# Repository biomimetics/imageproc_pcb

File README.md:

imageproc-pcb
=============

ImageProc printed circuit board

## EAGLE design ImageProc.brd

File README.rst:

This work is licensed under the `Creative Commons Attribution 3.0
Unported License <http://creativecommons.org/licenses/by/3.0/>`_.

================================
ImageProc printed circuit boards
================================

Description:
 ImageProc family of printed circuit boards, which use Microchip's dsPIC
 architecture.

Download boards:
 https://github.com/biomimetics/imageproc_pcb

Citing the boards:
 If you would like to reference these boards in a publication, please
 refer to the url and cite these conference papers:

 - *For ImageProc v.1.x:*

   | Fernando L. Garcia Bermudez and Ronald S. Fearing (2009)
   | `Optical Flow on a Flapping Wing Robot
     <http://dx.doi.org/10.1109/IROS.2009.5354337>`_
   | In IROS 2009. St. Louis, MO, USA.

 - *For ImageProc v.2.0-v2.4-x:*

   | Stanley S. Baek, Fernando L. Garcia Bermudez, and Ronald S. Fearing (2011)
   | `Flight Control for Target Seeking by 13 gram Ornithopter
     <http://dx.doi.org/10.1109/IROS.2011.6094581>`_
   | In IROS 2011. San Francisco, CA, USA.

 - *For ImageProc v2.5-x:*

   | Ryan C. Julian, Douglas D. Hutchings, and Ronald S. Fearing (2012)
   | This design is pending publication.

 This material is based upon work supported by the National Science
 Foundation under Grant No. IIS-0705429 and IIS-0931463. Any opinions,
 findings, and conclusions or recommendations expressed in this material
 are those of the author(s) and do not necessarily reflect the views of
 the National Science Foundation.

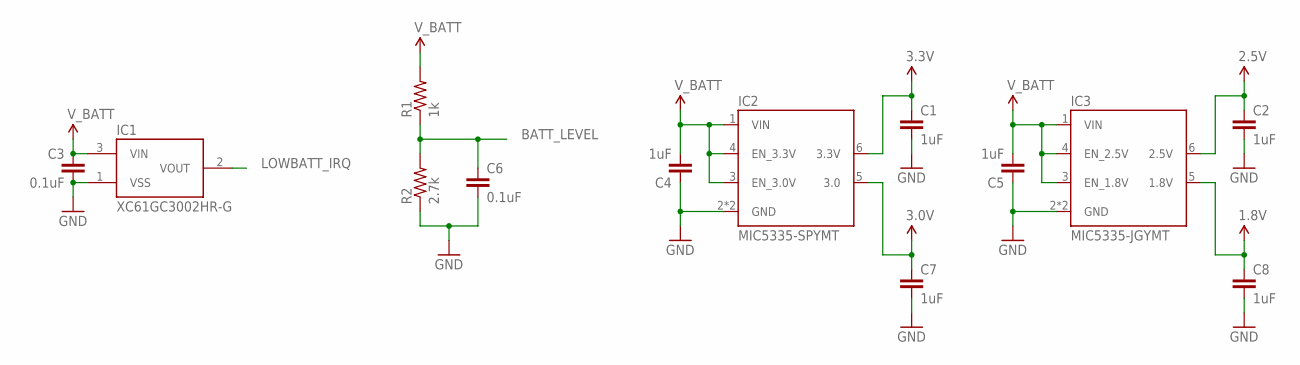
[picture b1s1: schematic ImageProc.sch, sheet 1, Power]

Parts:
C1, C2, C4, C5, C7, C8: 1uF; 0402-CAP
C3, C6: 0.1uF; 0402-CAP
IC1: XC61GC3002HR-G; USP-3
IC2: MIC5335-SPYMT; MLF-6
IC3: MIC5335-JGYMT; MLF-6
R1: 1k; 0402-RES
R2: 2.7k; 0402-RES

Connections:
1.8V: C8.1, IC3.5 (1.8V); also elsewhere on the board
2.5V: C2.1, IC3.6 (2.5V); also elsewhere on the board
3.0V: C7.1, IC2.5 (3.0)
3.3V: C1.1, IC2.6 (3.3V); also elsewhere on the board
BATT_LEVEL: C6.1, R1.1, R2.2; also elsewhere on the board
GND: C1.2, C2.2, C3.2, C4.1, C5.1, C6.2, C7.2, C8.2, IC1.1 (VSS), IC2.2 (GND), IC2.EPAD (GND), IC3.2 (GND), IC3.EPAD (GND), R2.1; also elsewhere on the board
LOWBATT_IRQ: IC1.2 (VOUT); also elsewhere on the board
V_BATT: C3.1, C4.2, C5.2, IC1.3 (VIN), IC2.1 (VIN), IC2.3 (EN_3.0V), IC2.4 (EN_3.3V), IC3.1 (VIN), IC3.3 (EN_1.8V), IC3.4 (EN_2.5V), R1.2; also elsewhere on the board

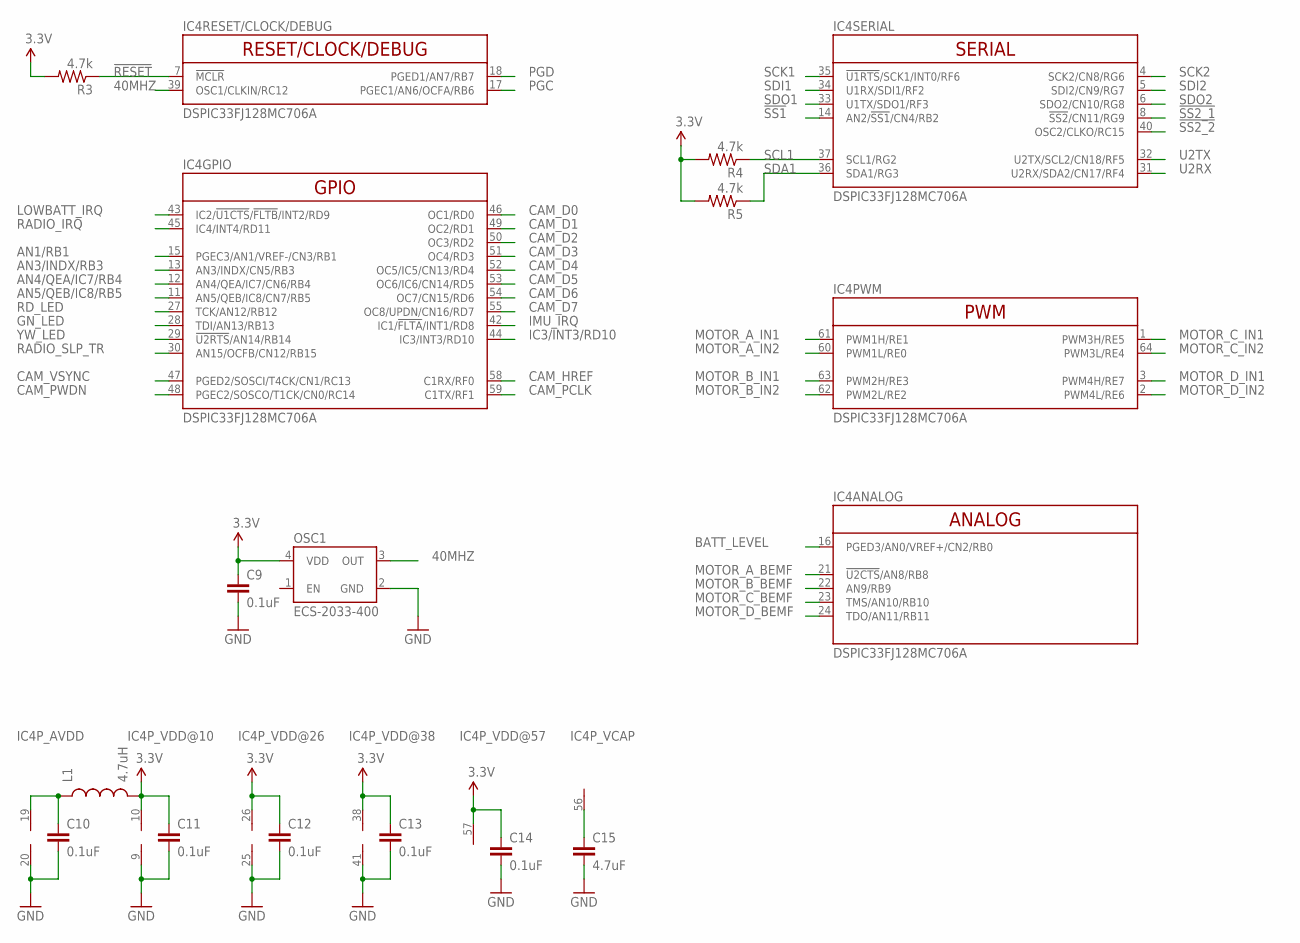
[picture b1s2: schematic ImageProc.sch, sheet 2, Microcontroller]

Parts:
C9, C10, C11, C12, C13, C14: 0.1uF; 0402-CAP
C15: 4.7uF; 0603-CAP; VOLTAGE 16V
IC4: DSPIC33FJ128MC706A; TQFP-64
L1: 4.7uH; 0603
OSC1: ECS-2033-400; OSCILLATOR-SMD
R3, R4, R5: 4.7k; 0402-RES

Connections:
3.3V: C9.1, C11.1, C12.1, C13.1, C14.1, IC4.10 (V+), IC4.26 (V+), IC4.38 (V+), IC4.57 (V+), L1.2, OSC1.4 (VDD), R3.2, R4.2, R5.2; also elsewhere on the board
40MHZ: IC4.39 (OSC1/CLKIN/RC12), OSC1.3 (OUT); also elsewhere on the board
!RESET: IC4.7 (!MCLR), R3.1; also elsewhere on the board
!SS1: IC4.14 (AN2/!SS1!/CN4/RB2); also elsewhere on the board
!SS2_1: IC4.8 (!SS2!/CN11/RG9); also elsewhere on the board
!SS2_2: IC4.40 (OSC2/CLKO/RC15); also elsewhere on the board
AN1/RB1: IC4.15 (PGEC3/AN1/VREF-/CN3/RB1); also elsewhere on the board
AN3/INDX/RB3: IC4.13 (AN3/INDX/CN5/RB3); also elsewhere on the board
AN4/QEA/IC7/RB4: IC4.12 (AN4/QEA/IC7/CN6/RB4); also elsewhere on the board
AN5/QEB/IC8/RB5: IC4.11 (AN5/QEB/IC8/CN7/RB5); also elsewhere on the board
BATT_LEVEL: IC4.16 (PGED3/AN0/VREF+/CN2/RB0); also elsewhere on the board
CAM_D0: IC4.46 (OC1/RD0); also elsewhere on the board
CAM_D1: IC4.49 (OC2/RD1); also elsewhere on the board
CAM_D2: IC4.50 (OC3/RD2); also elsewhere on the board
CAM_D3: IC4.51 (OC4/RD3); also elsewhere on the board
CAM_D4: IC4.52 (OC5/IC5/CN13/RD4); also elsewhere on the board
CAM_D5: IC4.53 (OC6/IC6/CN14/RD5); also elsewhere on the board
CAM_D6: IC4.54 (OC7/CN15/RD6); also elsewhere on the board
CAM_D7: IC4.55 (OC8/UPDN/CN16/RD7); also elsewhere on the board
CAM_HREF: IC4.58 (C1RX/RF0); also elsewhere on the board
CAM_PCLK: IC4.59 (C1TX/RF1); also elsewhere on the board
CAM_PWDN: IC4.48 (PGEC2/SOSCO/T1CK/CN0/RC14); also elsewhere on the board
CAM_VSYNC: IC4.47 (PGED2/SOSCI/T4CK/CN1/RC13); also elsewhere on the board
GND: C9.2, C10.2, C11.2, C12.2, C13.2, C14.2, C15.2, IC4.9 (V-), IC4.20 (V-), IC4.25 (V-), IC4.41 (V-), OSC1.2 (GND); also elsewhere on the board
GN_LED: IC4.28 (TDI/AN13/RB13); also elsewhere on the board
IC3/INT3/RD10: IC4.44 (IC3/INT3/RD10); also elsewhere on the board
IMU_IRQ: IC4.42 (IC1/!FLTA!/INT1/RD8); also elsewhere on the board
LOWBATT_IRQ: IC4.43 (IC2/!U1CTS!/!FLTB!/INT2/RD9); also elsewhere on the board
MOTOR_A_BEMF: IC4.21 (!U2CTS!/AN8/RB8); also elsewhere on the board
MOTOR_A_IN1: IC4.61 (PWM1H/RE1); also elsewhere on the board
MOTOR_A_IN2: IC4.60 (PWM1L/RE0); also elsewhere on the board
MOTOR_B_BEMF: IC4.22 (AN9/RB9); also elsewhere on the board
MOTOR_B_IN1: IC4.63 (PWM2H/RE3); also elsewhere on the board
MOTOR_B_IN2: IC4.62 (PWM2L/RE2); also elsewhere on the board
MOTOR_C_BEMF: IC4.23 (TMS/AN10/RB10); also elsewhere on the board
MOTOR_C_IN1: IC4.1 (PWM3H/RE5); also elsewhere on the board
MOTOR_C_IN2: IC4.64 (PWM3L/RE4); also elsewhere on the board
MOTOR_D_BEMF: IC4.24 (TDO/AN11/RB11); also elsewhere on the board
MOTOR_D_IN1: IC4.3 (PWM4H/RE7); also elsewhere on the board
MOTOR_D_IN2: IC4.2 (PWM4L/RE6); also elsewhere on the board
unnamed: C10.1, IC4.19 (V+), L1.1
unnamed: C15.1, IC4.56 (V+)
PGC: IC4.17 (PGEC1/AN6/OCFA/RB6); also elsewhere on the board
PGD: IC4.18 (PGED1/AN7/RB7); also elsewhere on the board
RADIO_IRQ: IC4.45 (IC4/INT4/RD11); also elsewhere on the board
RADIO_SLP_TR: IC4.30 (AN15/OCFB/CN12/RB15); also elsewhere on the board
RD_LED: IC4.27 (TCK/AN12/RB12); also elsewhere on the board
SCK1: IC4.35 (!U1RTS!/SCK1/INT0/RF6); also elsewhere on the board
SCK2: IC4.4 (SCK2/CN8/RG6); also elsewhere on the board
SCL1: IC4.37 (SCL1/RG2), R4.1; also elsewhere on the board
SDA1: IC4.36 (SDA1/RG3), R5.1; also elsewhere on the board
SDI1: IC4.34 (U1RX/SDI1/RF2); also elsewhere on the board
SDI2: IC4.5 (SDI2/CN9/RG7); also elsewhere on the board
SDO1: IC4.33 (U1TX/SDO1/RF3); also elsewhere on the board
SDO2: IC4.6 (SDO2/CN10/RG8); also elsewhere on the board
U2RX: IC4.31 (U2RX/SDA2/CN17/RF4); also elsewhere on the board
U2TX: IC4.32 (U2TX/SCL2/CN18/RF5); also elsewhere on the board
YW_LED: IC4.29 (!U2RTS!/AN14/RB14); also elsewhere on the board

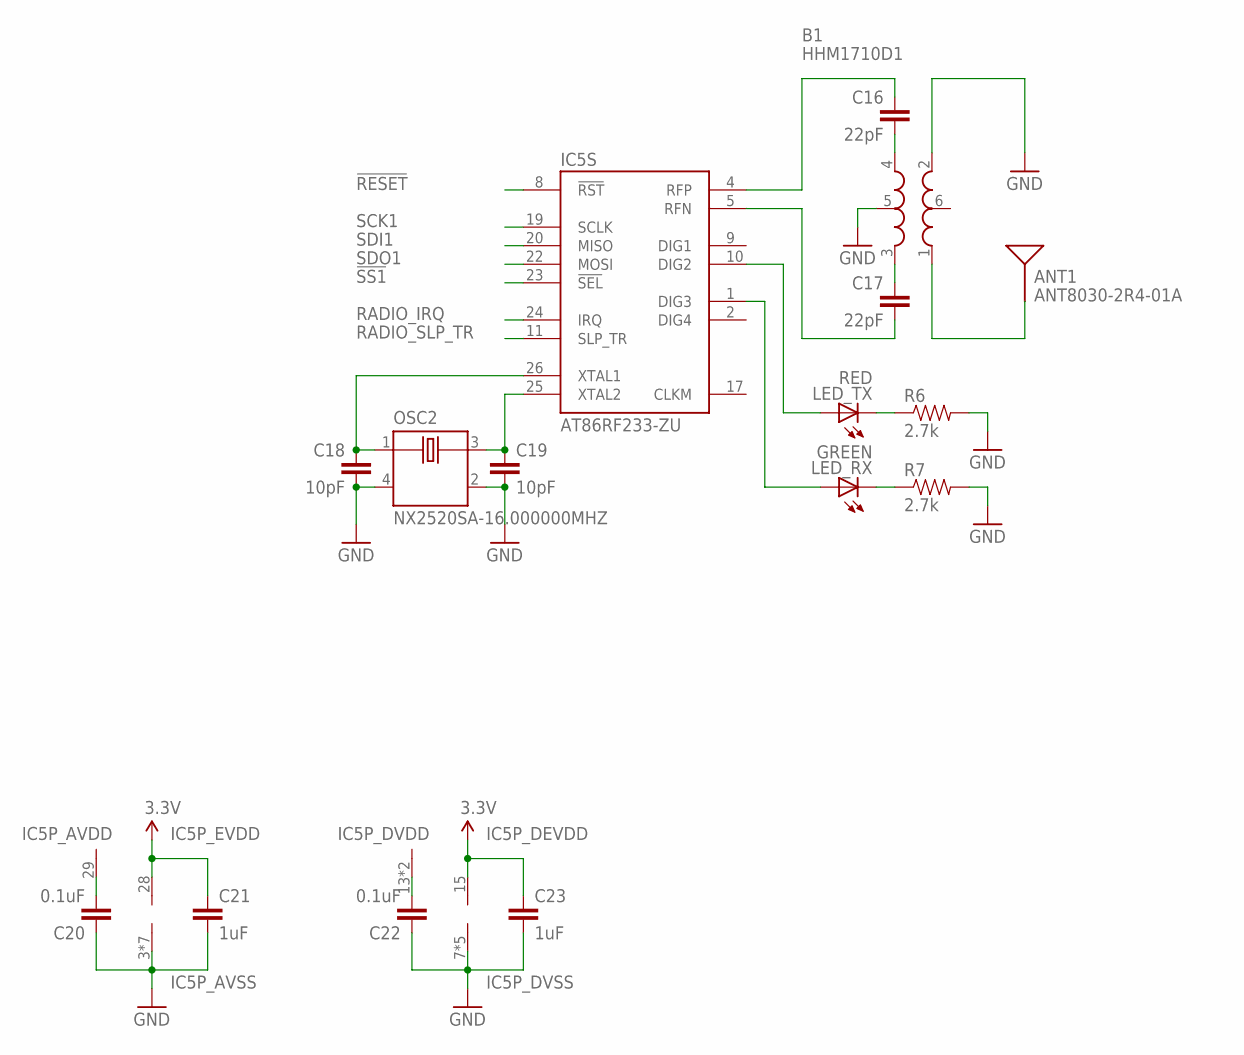
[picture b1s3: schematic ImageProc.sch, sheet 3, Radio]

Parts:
ANT1: ANT8030-2R4-01A
B1: HHM1710D1; 0603-BALUN
C16, C17: 22pF; 0402-CAP; TOLERANCE 5%; VOLTAGE 50V
C18, C19: 10pF; 0402-CAP; TOLERANCE 10%; VOLTAGE 50V
C20, C22: 0.1uF; 0402-CAP; TOLERANCE 10%; VOLTAGE 16V
C21, C23: 1uF; 0402-CAP; TOLERANCE 10%; VOLTAGE 16V
IC5: AT86RF233-ZU; VQFN-32QN2
LED_RX: GREEN; LED-0603
LED_TX: RED; LED-0603
OSC2: NX2520SA-16.000000MHZ; CRYSTAL-SMD
R6, R7: 2.7k; 0402-RES

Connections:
3.3V: C21.1, C23.1, IC5.15 (V+), IC5.28 (V+); also elsewhere on the board
!RESET: IC5.8 (!RST); also elsewhere on the board
!SS1: IC5.23 (!SEL); also elsewhere on the board
GND: B1.2 (RFGND), B1.5 (GND), C18.2, C19.2, C20.1, C21.2, C22.1, C23.2, IC5.3 (V-), IC5.6 (V-), IC5.7 (V-), IC5.12 (V-), IC5.16 (V-), IC5.18 (V-), IC5.21 (V-), IC5.27 (V-), IC5.30 (V-), IC5.31 (V-), IC5.32 (V-), IC5.PAD (V-), OSC2.2 (GND), OSC2.4 (GND), R6.2, R7.2; also elsewhere on the board
unnamed: C22.2, IC5.13 (V+), IC5.14 (V+)
unnamed: C20.2, IC5.29 (V+)
unnamed: ANT1.A, B1.1 (UNBAL)
unnamed: LED_TX.C, R6.1
unnamed: C16.1, IC5.4 (RFP)
unnamed: C17.2, IC5.5 (RFN)
unnamed: C19.1, IC5.25 (XTAL2), OSC2.3 (OUT/IN)
unnamed: C18.1, IC5.26 (XTAL1), OSC2.1 (IN/OUT)
unnamed: B1.3 (BAL3), C17.1
unnamed: LED_RX.C, R7.1
unnamed: B1.4 (BAL4), C16.2
unnamed: IC5.1 (DIG3), LED_RX.A
unnamed: IC5.10 (DIG2), LED_TX.A
RADIO_IRQ: IC5.24 (IRQ); also elsewhere on the board
RADIO_SLP_TR: IC5.11 (SLP_TR); also elsewhere on the board
SCK1: IC5.19 (SCLK); also elsewhere on the board
SDI1: IC5.20 (MISO); also elsewhere on the board
SDO1: IC5.22 (MOSI); also elsewhere on the board

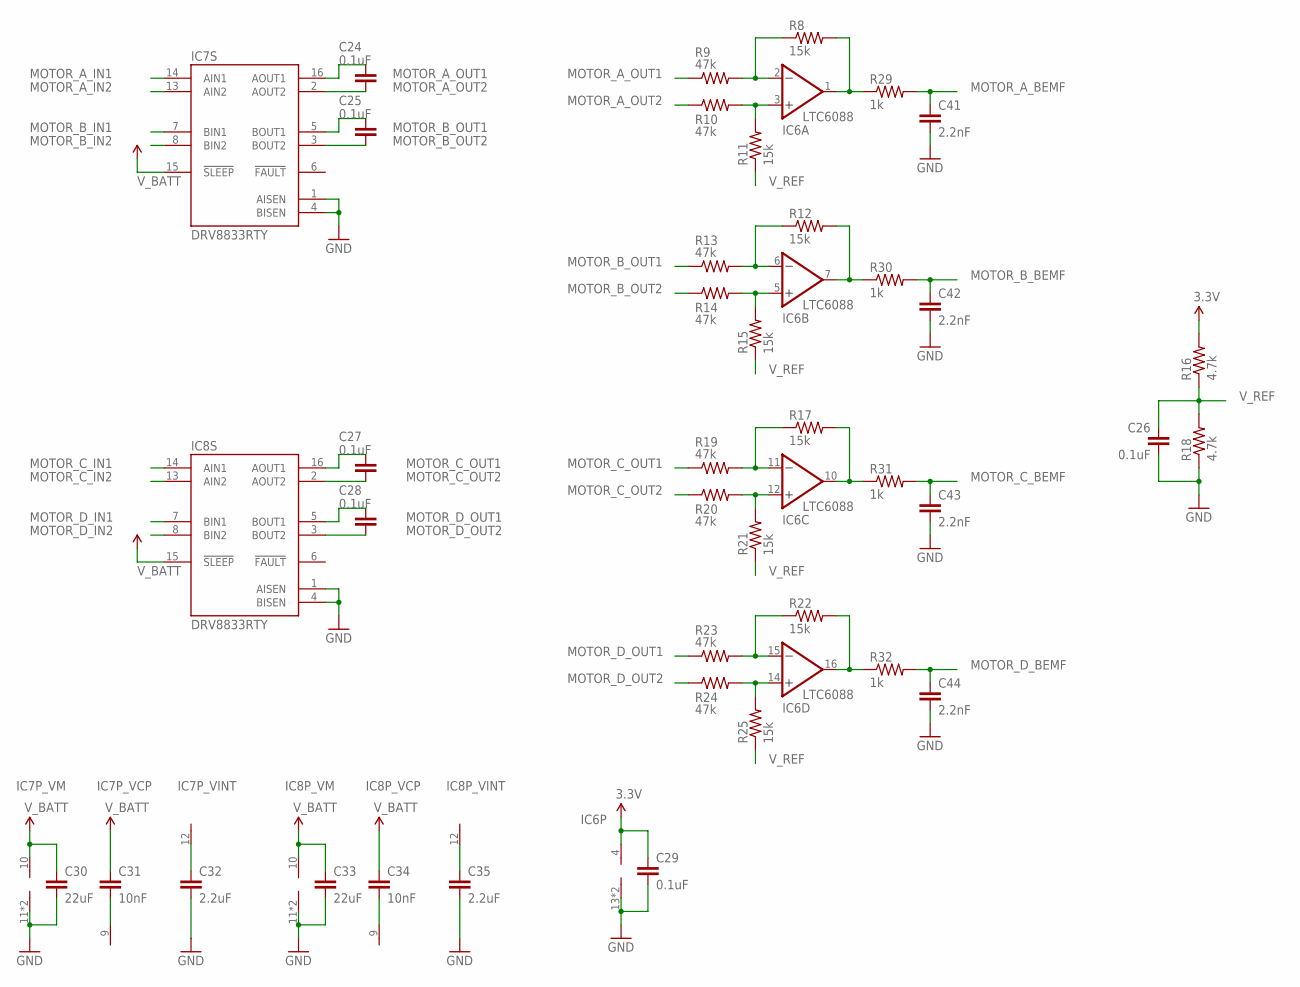
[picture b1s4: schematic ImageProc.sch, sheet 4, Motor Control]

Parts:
C24, C25, C27, C28: 0.1uF; 0402-CAP; VOLTAGE 10V
C26, C29: 0.1uF; 0402-CAP
C30, C33: 22uF; 0603-CAP
C31, C34: 10nF; 0402-CAP; VOLTAGE 16V
C32, C35: 2.2uF; 0402-CAP; VOLTAGE 6.3V
C41, C42, C43, C44: 2.2nF; 0402-CAP
IC6: LTC6088; DFN-16
IC7, IC8: DRV8833RTY; S-PWQFN-N16
R8, R11, R12, R15, R17, R21, R22, R25: 15k; 0402-RES; TOLERANCE 1%
R9, R10, R13, R14, R19, R20, R23, R24: 47k; 0402-RES; TOLERANCE 1%
R16, R18: 4.7k; 0402-RES; TOLERANCE 1%
R29, R30, R31, R32: 1k; 0402-RES

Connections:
3.3V: C29.1, IC6.4 (V+), R16.2; also elsewhere on the board
GND: C26.2, C29.2, C30.2, C32.2, C33.2, C35.2, C41.2, C42.2, C43.2, C44.2, IC6.13 (V-), IC6.PAD (V-), IC7.1 (AISEN), IC7.4 (BISEN), IC7.11 (V-), IC7.PPAD (V-), IC8.1 (AISEN), IC8.4 (BISEN), IC8.11 (V-), IC8.PPAD (V-), R18.1; also elsewhere on the board
MOTOR_A_BEMF: C41.1, R29.2; also elsewhere on the board
MOTOR_A_IN1: IC7.14 (AIN1); also elsewhere on the board
MOTOR_A_IN2: IC7.13 (AIN2); also elsewhere on the board
MOTOR_A_OUT1: C24.1, IC7.16 (AOUT1), R9.1; also elsewhere on the board
MOTOR_A_OUT2: C24.2, IC7.2 (AOUT2), R10.1; also elsewhere on the board
MOTOR_B_BEMF: C42.1, R30.2; also elsewhere on the board
MOTOR_B_IN1: IC7.7 (BIN1); also elsewhere on the board
MOTOR_B_IN2: IC7.8 (BIN2); also elsewhere on the board
MOTOR_B_OUT1: C25.1, IC7.5 (BOUT1), R13.1; also elsewhere on the board
MOTOR_B_OUT2: C25.2, IC7.3 (BOUT2), R14.1; also elsewhere on the board
MOTOR_C_BEMF: C43.1, R31.2; also elsewhere on the board
MOTOR_C_IN1: IC8.14 (AIN1); also elsewhere on the board
MOTOR_C_IN2: IC8.13 (AIN2); also elsewhere on the board
MOTOR_C_OUT1: C27.1, IC8.16 (AOUT1), R19.1; also elsewhere on the board
MOTOR_C_OUT2: C27.2, IC8.2 (AOUT2), R20.1; also elsewhere on the board
MOTOR_D_BEMF: C44.1, R32.2; also elsewhere on the board
MOTOR_D_IN1: IC8.7 (BIN1); also elsewhere on the board
MOTOR_D_IN2: IC8.8 (BIN2); also elsewhere on the board
MOTOR_D_OUT1: C28.1, IC8.5 (BOUT1), R23.1; also elsewhere on the board
MOTOR_D_OUT2: C28.2, IC8.3 (BOUT2), R24.1; also elsewhere on the board
unnamed: C31.2, IC7.9 (V+)
unnamed: C32.1, IC7.12 (V-)
unnamed: C34.2, IC8.9 (V+)
unnamed: C35.1, IC8.12 (V-)
unnamed: IC6.6 (-IN), R12.1, R13.2
unnamed: IC6.5 (+IN), R14.2, R15.2
unnamed: IC6.11 (-IN), R17.1, R19.2
unnamed: IC6.12 (+IN), R20.2, R21.2
unnamed: IC6.15 (-IN), R22.1, R23.2
unnamed: IC6.14 (+IN), R24.2, R25.2
unnamed: IC6.2 (-IN), R8.1, R9.2
unnamed: IC6.3 (+IN), R10.2, R11.2
unnamed: IC6.16 (OUT), R22.2, R32.1
unnamed: IC6.10 (OUT), R17.2, R31.1
unnamed: IC6.1 (OUT), R8.2, R29.1
unnamed: IC6.7 (OUT), R12.2, R30.1
V_BATT: C30.1, C31.1, C33.1, C34.1, IC7.10 (V+), IC7.15 (!SLEEP), IC8.10 (V+), IC8.15 (!SLEEP); also elsewhere on the board
V_REF: C26.1, R11.1, R15.1, R16.1, R18.2, R21.1, R25.1

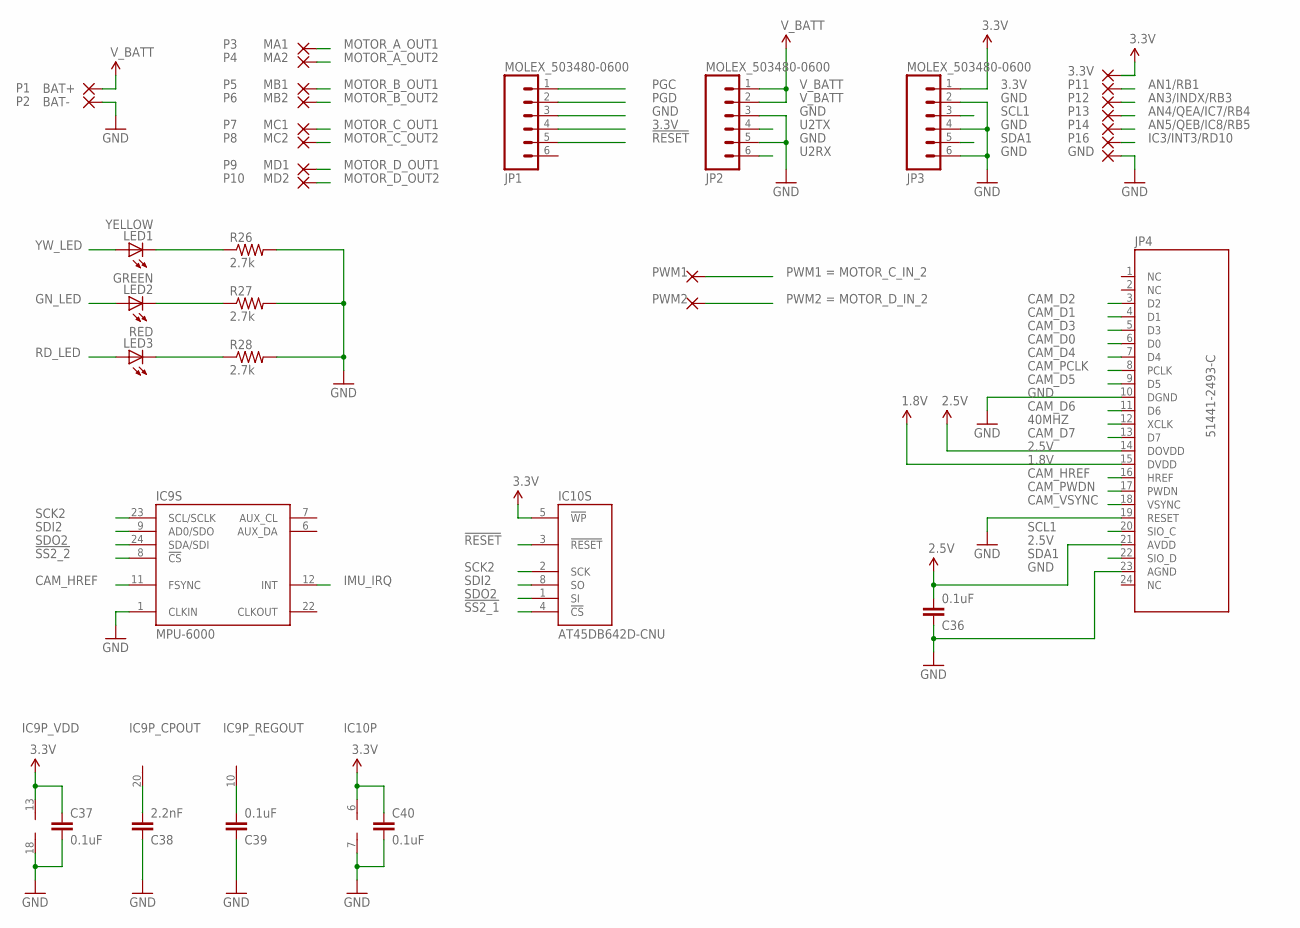
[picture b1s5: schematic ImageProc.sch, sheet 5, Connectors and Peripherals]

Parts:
3.3V: EXT5; SMD1,27-2,54
C36, C40: 0.1uF; 0402-CAP
C37: 0.1uF; 0402-CAP; TOLERANCE 10%; VOLTAGE 4V
C38: 2.2nF; 0402-CAP; TOLERANCE 10%; VOLTAGE 50V
C39: 0.1uF; 0402-CAP; TOLERANCE 10%; VOLTAGE 2V
GND: EXT5; SMD1,27-2,54
IC9: MPU-6000; QFN-24
IC10: AT45DB642D-CNU; CASON-8
JP1, JP2, JP3: MOLEX_503480-0600
JP4: 51441-2493-C; MOLEX_52740-2490
LED1: YELLOW; LED-0603
LED2: GREEN; LED-0603
LED3: RED; LED-0603
P1: BAT+; SMD1,27-2,54
P2: BAT-; SMD1,27-2,54
P3: MA1; SMD1,27-2,54
P4: MA2; SMD1,27-2,54
P5: MB1; SMD1,27-2,54
P6: MB2; SMD1,27-2,54
P7: MC1; SMD1,27-2,54
P8: MC2; SMD1,27-2,54
P9: MD1; SMD1,27-2,54
P10: MD2; SMD1,27-2,54
P11: EXT1; SMD1,27-2,54
P12: EXT2; SMD1,27-2,54
P13: EXT3; SMD1,27-2,54
P14: EXT4; SMD1,27-2,54
P16: EXT5; SMD1,27-2,54
PWM1, PWM2: EXT5; SMD1,27-2,54
R26, R27, R28: 2.7k; 0402-RES

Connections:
1.8V: JP4.15 (DVDD); also elsewhere on the board
2.5V: C36.2, JP4.14 (DOVDD), JP4.21 (AVDD); also elsewhere on the board
3.3V: 3.3V.1, C37.1, C40.1, IC9.13 (V+), IC10.5 (!WP), IC10.6 (V+), JP1.4, JP3.1; also elsewhere on the board
40MHZ: JP4.12 (XCLK); also elsewhere on the board
!RESET: IC10.3 (!RESET), JP1.5; also elsewhere on the board
!SS2_1: IC10.4 (!CS); also elsewhere on the board
!SS2_2: IC9.8 (!CS); also elsewhere on the board
AN1/RB1: P11.1; also elsewhere on the board
AN3/INDX/RB3: P12.1; also elsewhere on the board
AN4/QEA/IC7/RB4: P13.1; also elsewhere on the board
AN5/QEB/IC8/RB5: P14.1; also elsewhere on the board
CAM_D0: JP4.6 (D0); also elsewhere on the board
CAM_D1: JP4.4 (D1); also elsewhere on the board
CAM_D2: JP4.3 (D2); also elsewhere on the board
CAM_D3: JP4.5 (D3); also elsewhere on the board
CAM_D4: JP4.7 (D4); also elsewhere on the board
CAM_D5: JP4.9 (D5); also elsewhere on the board
CAM_D6: JP4.11 (D6); also elsewhere on the board
CAM_D7: JP4.13 (D7); also elsewhere on the board
CAM_HREF: IC9.11 (FSYNC), JP4.16 (HREF); also elsewhere on the board
CAM_PCLK: JP4.8 (PCLK); also elsewhere on the board
CAM_PWDN: JP4.17 (PWDN); also elsewhere on the board
CAM_VSYNC: JP4.18 (VSYNC); also elsewhere on the board
GND: C36.1, C37.2, C38.1, C39.1, C40.2, GND.1, IC9.1 (CLKIN), IC9.18 (V-), IC10.7 (V-), JP1.3, JP2.3, JP2.5, JP3.2, JP3.4, JP3.6, JP4.10 (DGND), JP4.19 (RESET), JP4.23 (AGND), P2.1, R26.2, R27.2, R28.2; also elsewhere on the board
GN_LED: LED2.A; also elsewhere on the board
IC3/INT3/RD10: P16.1; also elsewhere on the board
IMU_IRQ: IC9.12 (INT); also elsewhere on the board
MOTOR_A_OUT1: P3.1; also elsewhere on the board
MOTOR_A_OUT2: P4.1; also elsewhere on the board
MOTOR_B_OUT1: P5.1; also elsewhere on the board
MOTOR_B_OUT2: P6.1; also elsewhere on the board
MOTOR_C_IN2: PWM1.1; also elsewhere on the board
MOTOR_C_OUT1: P7.1; also elsewhere on the board
MOTOR_C_OUT2: P8.1; also elsewhere on the board
MOTOR_D_IN2: PWM2.1; also elsewhere on the board
MOTOR_D_OUT1: P9.1; also elsewhere on the board
MOTOR_D_OUT2: P10.1; also elsewhere on the board
unnamed: LED1.C, R26.1
unnamed: LED2.C, R27.1
unnamed: LED3.C, R28.1
unnamed: C38.2, IC9.20 (V-)
unnamed: C39.2, IC9.10 (V-)
PGC: JP1.1; also elsewhere on the board
PGD: JP1.2; also elsewhere on the board
RD_LED: LED3.A; also elsewhere on the board
SCK2: IC9.23 (SCL/SCLK), IC10.2 (SCK); also elsewhere on the board
SCL1: JP3.3, JP4.20 (SIO_C); also elsewhere on the board
SDA1: JP3.5, JP4.22 (SIO_D); also elsewhere on the board
SDI2: IC9.9 (AD0/SDO), IC10.8 (SO); also elsewhere on the board
SDO2: IC9.24 (SDA/SDI), IC10.1 (SI); also elsewhere on the board
U2RX: JP2.6; also elsewhere on the board
U2TX: JP2.4; also elsewhere on the board
V_BATT: JP2.1, JP2.2, P1.1; also elsewhere on the board
YW_LED: LED1.A; also elsewhere on the board

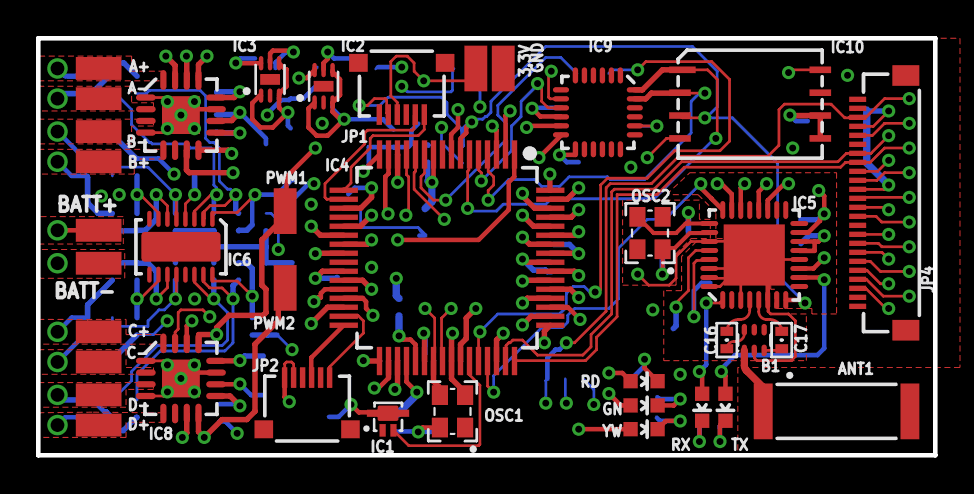
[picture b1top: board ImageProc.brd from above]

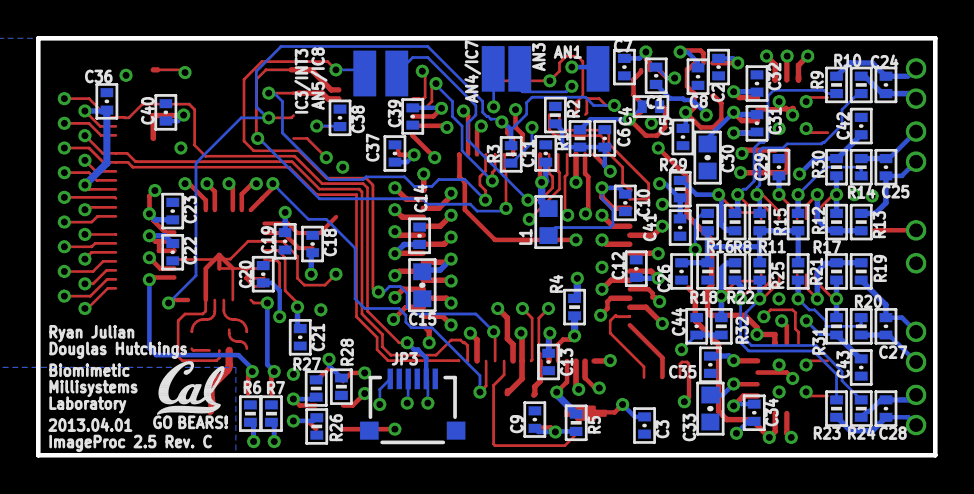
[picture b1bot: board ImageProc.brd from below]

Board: 4 copper layers, 49.8 x 23.2 mm, 119 parts (81 on the bottom side), 105 nets.

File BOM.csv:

Qty to build:,20,,,,,,,,,,,,
Revision:,1,,,,,,,,,,,,
Quantity,Designator,Description,Value,Manufacturer,Part Number,Distributor,Distributor Part #,Incl. In Kit,Need for Build,Qty. To Return,Comments, Unit Price ,Build price
20,"C3, C6, C9, C10, C11, C12, C13, C14, C20, C22, C24, C25, C26, C27, C28, C29, C36, C37, C39, C40",CAP CER 0.1UF 16V 10% X7R 0402,0.1uF,Murata,GRM155R71C104KA88D,Digi-Key,490-3261-1-ND,N/A,400,N/A,, $0.00632 , $0.13 
2,"C31, C34",CAP CER 10000PF 25V 10% X8R 0402,10nF,TDK,C1005X8R1E103K050BA,Digi-Key,445-2494-1-ND,N/A,40,N/A,, $0.12400 , $2.48 
2,"C18, C19",CAP CER 10PF 50V 5% NPO 0402,10pF,Yageo,CC0402JRNPO9BN100,Digi-Key,311-1014-2-ND,N/A,40,N/A,, $0.00920 , $0.18 
8,"R8, R11, R12, R15, R17, R21, R22, R25",RES 15K OHM 1/10W 1% 0402 SMD,15k,Panasonic,ERJ-2RKF1502X,Digi-Key,P15.0KLCT-ND,N/A,160,N/A,, $0.01840 , $0.37 
5,"R1, R29, R30, R31, R32",RES 1K OHM 1/10W 5% 0402 SMD,1k,Panasonic,ERJ-2GEJ102X,Digi-Key,P1.0KJCT-ND,N/A,100,N/A,, $0.01310 , $0.26 
8,"C1, C2, C4, C5, C7, C8, C21, C23",CAP CER 1UF 16V 10% X5R 040,1uF,TDK,C1005X5R1C105K050BC,Digi-Key,445-4978-1-ND,N/A,160,N/A,, $0.03800 , $0.76 
5,"C38, C41, C42, C43, C44",CAP CER 2200PF 50V 10% X7R 0402,2.2nF,Taiyo Yuden,UMK105B7222KV-F,Digi-Key,587-1221-1-ND,N/A,100,N/A,, $0.00660 , $0.13 
2,"C32, C35",CAP CER 2.2UF 10V 20% X5R 0402,2.2uF,Taiyo Yuden,LMK105BJ225MV-F,Digi-Key,587-3153-1-ND,N/A,40,N/A,, $0.12800 , $2.56 
6,"R2, R6, R7, R26, R27, R28",RES 2.7K OHM 1/10W 5% 0402 SMD,2.7k,Panasonic,ERJ-2GEJ272X,Digi-Key,P2.7KJCT-ND,N/A,120,N/A,, $0.00131 , $0.03 
2,"C16, C17",CAP CER 22PF 50V 5% NP0 0402,22pF,Murata,GRM1555C1H220JZ01D,Digi-Key,490-1283-1-ND,N/A,40,N/A,, $0.02800 , $0.56 
2,"C30, C33",CAP CER 22UF 6.3V 20% X5R 0603,22uF,TDK,C1608X5R0J226M080AC,Digi-Key,445-8028-1-ND,N/A,40,N/A,, $0.33600 , $6.72 
5,"R3, R4, R5, R16, R18",RES 4.7K OHM 1/10W 1% 0402 SMD,4.7k,Panasonic,ERJ-2RKF4701X,Digi-Key,P4.70KLCT-ND,N/A,100,N/A,, $0.01840 , $0.37 
1,C15,CAP CER 4.7UF 16V 10% X5R 0603,4.7uF,Taiyo Yuden,EMK107ABJ475KA-T,Digi-Key,587-2786-1-ND,N/A,20,N/A,, $0.21600 , $4.32 
1,L1,INDUCTOR MULTILAYER 4.7UH 0603,4.7uH,TDK,MLF1608A4R7K,Digi-Key,445-1021-1-ND,N/A,20,N/A,, $0.17000 , $3.40 
8,"R9, R10, R13, R14, R19, R20, R23, R24",RES 47K OHM 1/10W 1% 0402 SMD,47k,Panasonic,ERJ-2RKF4702X,Digi-Key,P47.0KLCT-ND,N/A,160,N/A,, $0.01840 , $0.37 
1,JP4,24-position SMD ZIF FPC connector,,Molex,51441-2493-C,Digi-Key,Do not populate,N/A,20,N/A,Not to be populated during assembly,, $-   
1,ANT1,Chip Mulitlayer Antenna for 2.4 GHz W-LAN / Bluetooth,,TDK,ANT8030-2R4-01A,Digi-Key,445-3719-1-ND,N/A,20,N/A,, $4.56700 , $91.34 
1,IC10,64-megabit 2.7V Dual-interface DataFlash,,Atmel,AT45DB642D-CNU,Digi-Key,AT45DB642D-CNU-ND,N/A,20,N/A,, $5.81000 , $116.20 
1,IC5,"Low Power, 2.4GHz Transceiver for ZigBee, RF4CE, IEEE 802.15.4, 6LoWPAN, and ISM Applications", ,Atmel,AT86RF233-ZU,Digi-Key,AT86RF233-ZU-ND,N/A,20,N/A,, $4.73000 , $94.60 
2,"IC7, IC8",Dual H-Bridge Motor Driver,,TI,DRV8833RTY,Digi-Key,296-29513-1-ND,N/A,40,N/A,, $2.55440 , $51.09 
1,IC4,"16-bit Digital Signal Controllers (up to 256 KB Flash and 
30 KB SRAM) with Motor Control and Advanced Analog", ,Microchip,DSPIC33FJ128MC706A-I/PT,Digi-Key,DSPIC33FJ128MC706A-H/PT-ND,N/A,20,N/A,, $8.17000 , $163.40 
1,OSC1,3.3V 40MHz subminiature SMD oscillator,,ECS,ECS-2033-400,Digi-Key,XC1437CT-ND,N/A,20,N/A,, $2.87300 , $57.46 
2,"LED2, LED_RX",LED GREEN CLEAR 0603 SMD,,Lite-On,LTST-C190KGKT,Digi-Key,160-1435-1-ND,N/A,40,N/A,, $0.22800 , $4.56 
1,B1,Multilayer Balun Transformers for 2.4GHz W-LAN/Bluetooth,,TDK,HHM1710D1,Digi-Key,445-3246-1-ND,N/A,20,N/A,, $2.18300 , $43.66 
1,IC6,"14MHz, Rail-to-Rail Output, 12nV/Hz, 1.1mA Op Amp",,Linear,LTC6088CDHC,Digi-Key,LTC6088HDHC#PBF-ND,N/A,20,N/A,, $3.42000 , $68.40 
1,IC3,150mA  dual (2.5V/1.8V) voltage regulator,,Micrel,MIC5335-JGYMT,Digi-Key,576-3589-1-ND,N/A,20,N/A,, $1.98000 , $39.60 
1,IC2,150mA dual (3.3V/3.0V) voltage regulator,,Micrel,MIC5335-SPYMT,Digi-Key,576-1949-1-ND,N/A,20,N/A,, $1.98000 , $39.60 
3,"JP1, JP2, JP3",CONN .5MM FPC 6POS RA SMD B-FLIP,,Molex,503480-0600,Digi-Key,WM1387DKR-ND,N/A,60,N/A,, $0.64380 , $12.88 
1,IC9,"MPU-6000 3-axis gyro + 3-axis accelerometer, SPI/I2C interface with auxiliary I2C interface for magnetometer", ,InvenSense,MPU-6000,InvenSense,MPU-6000,N/A,20,N/A,, $15.00000 , $300.00 
1,OSC2,CRYSTAL 16.000000MHZ 10PF SMD,,NDK,NX2520SA-16.000000MHZ,Digi-Key,644-1059-1-ND,N/A,20,N/A,, $1.83900 , $36.78 
2,"LED3, LED_TX",LED SUPER RED CLEAR 0603 SMD,,Lite-On,LTST-C190KRKT,Digi-Key,160-1436-1-ND,N/A,40,N/A,, $0.22800 , $4.56 
1,IC1,3.0V voltage detector,,Torex,XC61GC3002HR-G,Digi-Key,893-1046-1-ND,N/A,20,N/A,, $0.49400 , $9.88 
1,LED1,LED YELLOW CLEAR 0603 SMD,,Lite-On,LTST-C190KSKT,Digi-Key,160-1437-1-ND,N/A,20,N/A,, $0.24800 , $4.96

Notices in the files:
parts and their libraries:
biomimetic: UC Regents. All rights reserved.
